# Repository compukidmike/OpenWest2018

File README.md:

# OpenWest2018 Electronic Badge

## This year's badge is dedicated to our dear friend d3c4f. May his memory live on through many more awesome badges. 

The 2018 badge features WiFi connectivity, and all the badges are controlled by an MQTT server. The main controller is a WeMos D1 Mini, which uses the ESP8266 WiFi module.

**A note on battery life:** WiFi uses a lot of power. So do LEDs. The badges probably won't last more than a day on batteries. Take them out when you're not at the conference to avoid unnecessary battery drain. **Also, don't connect a USB cable while the batteries are in the badge. Bad things could happen.**

One of the fun things about this badge is that they're all controlled by this central server. There's no authentication on MQTT publications, so anyone can change what all the badges are doing. There are many programs to interact with MQTT servers. MQTTLens is a free chrome app that's very easy to use. If you want to learn more about MQTT go here https://www.hivemq.com/blog/mqtt-essentials-part-1-introducing-mqtt

We're using mosquitto (https://mosquitto.org/) for our local MQTT server. This server is only available at the conference. After the con is over, you'll have to connect the badge to your own server or an online service like adafruit.io. There are instructions below on how to do that.

The local MQTT server IP is 10.155.0.214, port 1883

The Feeds are setup as follows:
- Feed names: color1, color2, effect, effectspeed
- All feeds are prefixed by `feeds/`
- Colors are in Hex format (FFFFFF)
- Effectspeed is 0-255
- Effect is 0-6 (Off, On, Blink, Pulse, Alternate1, Alternate2, Rainbow)
- Must set retain flag on messages

The retain flag is important. It tells the server to keep the last message, and give it to any new client that subscribes to a feed. That means your badge won't have to wait until a new message is sent out to start displaying the proper colors, etc.

----------

## To get the Arduino IDE set up, you'll need to do the following:
(The Arduino IDE can be downloaded from https://www.arduino.cc/)
- Add the ESP8266 to the boards menu
  - From the Arduino IDE, click on File -> Preferences
  - Add this URL to the "Additional Boards Manager URLs" http://arduino.esp8266.com/stable/package_esp8266com_index.json
  - Click OK
  - Click on Tools > Board > Board Manager
  - Type ESP8266 in the search box
  - Find ESP8266 in the list and click Install
  
- Add the required libraries
  - Click Sketch > Include Library > Manage Libraries...
  - Search for and install the following libraries:
    - Adafruit IO Arduino
    - Adafruit MQTT Library
    - ArduinoHTTPClient
    - FastLED
    - WiFi
- Mac users need to download the WeMos driver at: https://wiki.wemos.cc/downloads (restart required after install).

## To connect the badge to your own WiFi network:
- Edit the following lines in the code:
  ```
  #define WLAN_SSID       "OPENWEST-GUEST"
  #define WLAN_PASS       "Openwest2018!"
  ```

## To connect the badge to a different MQTT server:
- Edit the following lines in the code:
  ```
  #define AIO_SERVER      "10.155.0.214"         // IP or URL for MQTT server
  #define AIO_SERVERPORT  1883                   // use 8883 for SSL
  #define AIO_USERNAME    "test"                 // Adafruit.io username
  #define AIO_KEY         "1234567890"           // Adafruit.io key
  ```
- To connect to adafruit.io, you'll need to create an account and then put your username and AIO key here. There are also more steps below for adafruit.io

## Adafruit.io Workaround
If you attended my talk about the badge, I talked about how adafruit.io is an MQTT server that doesn't fit the spec. One of the things I said was that they retain messages by default. Well, they changed that, but still don't support the retain flag, so there's a workaround. Please keep in mind that they made this change on April 22, 2018. I've been working with the badge code since long before that. They've updated their libraries to handle this, but I haven't had a chance to mess with it. If you get it working with the new Adafruit IO library, please submit a pull request.
Here's the blog post that talks about the change: https://io.adafruit.com/blog/notebook/2018/04/22/new-io-plus-and-mqtt-features/

### So, with that said, here's the workaround:
- All feed names are prefixed by your username, so they look like this: `<username>/feeds/<feed_name>`
- You'll need to set up a publish feed for each of your feed subscriptions with `/get` at the end (I know, it's ridiculous).
  - Example: ```Adafruit_MQTT_Publish color1get = Adafruit_MQTT_Publish(&mqtt, AIO_USERNAME "/feeds/color1/get");```
  - Note that the name must be different from the feed subscription (color1get vs color1)
- Then, near the bottom of the code after this line: ```Serial.println("MQTT Connected!");```
  - Add a publish for each feed:
    ```
    color1get.publish('\0');
    color2get.publish('\0');
    effectget.publish('\0');
    effectspeedget.publish('\0');
    delay(1000); //delay for receiving the packets
    ```
  - The delay is necessary to give time to get the response from the server and not drop packets
  
I know this is an ugly workaround. I'm sorry. On the bright side, it does show how to setup and publish data back to the server.

----------

If I missed anything, or you have something to add to this readme, please submit a pull request.

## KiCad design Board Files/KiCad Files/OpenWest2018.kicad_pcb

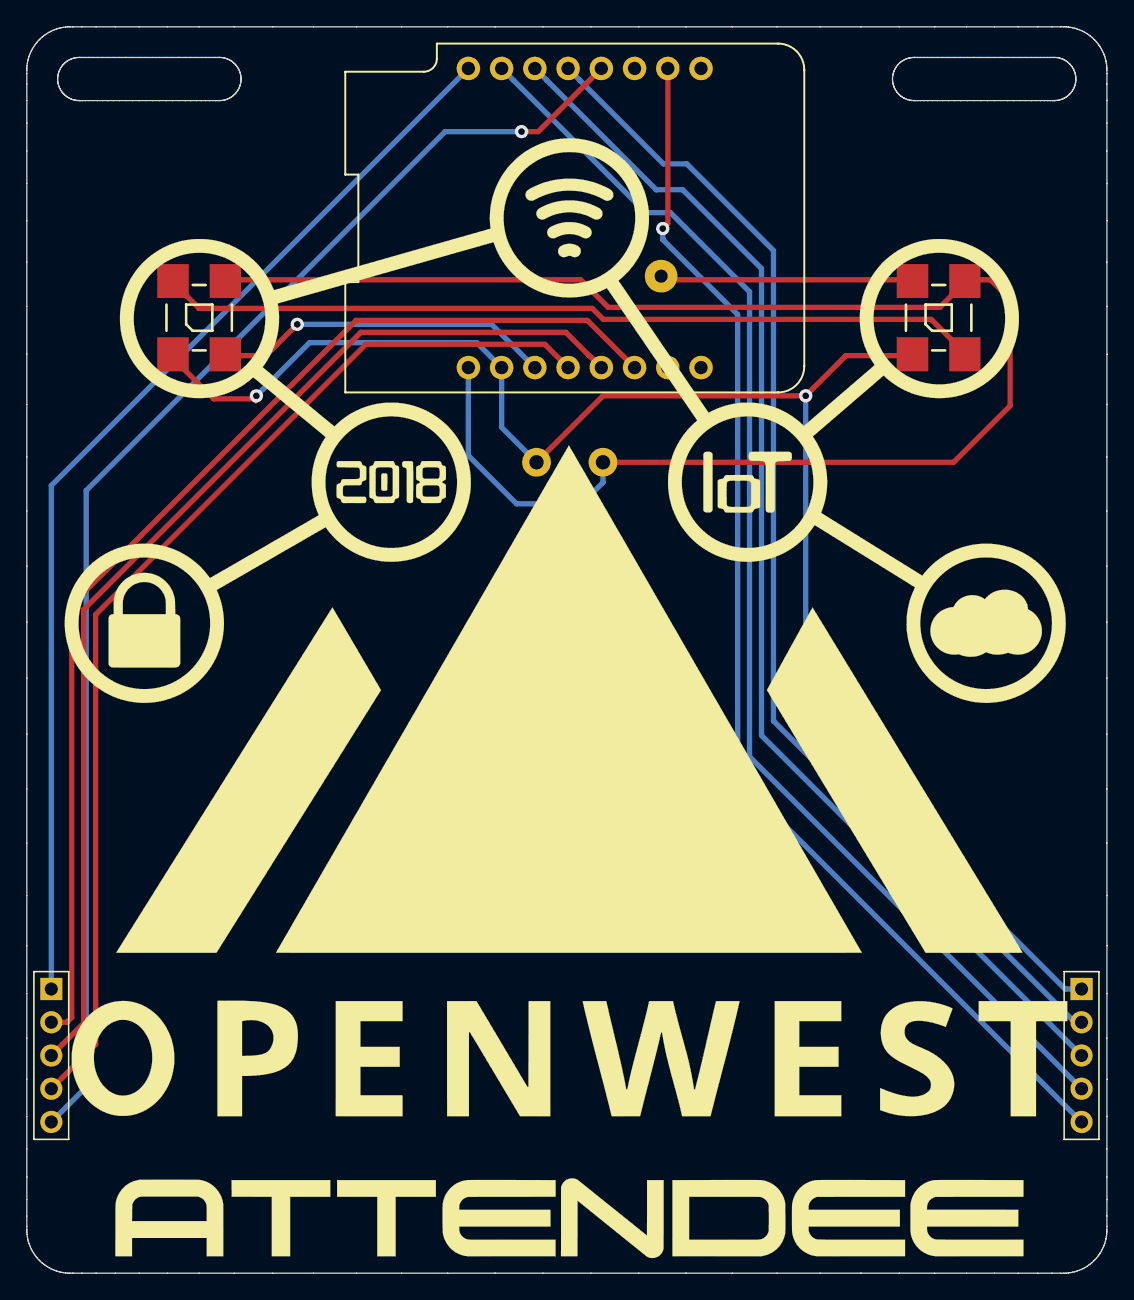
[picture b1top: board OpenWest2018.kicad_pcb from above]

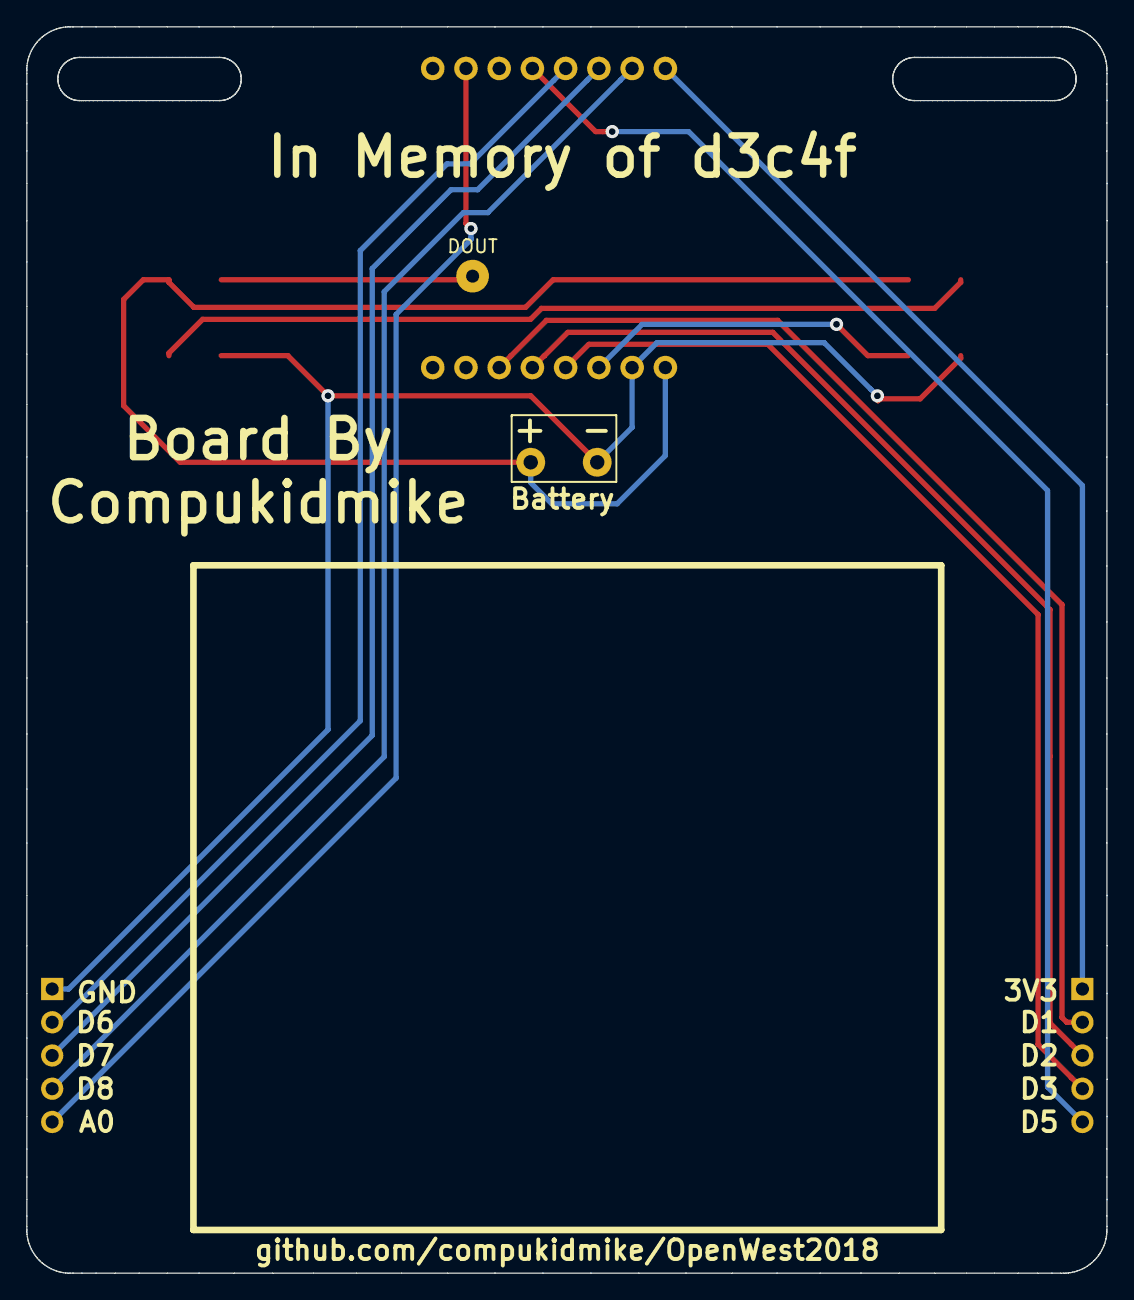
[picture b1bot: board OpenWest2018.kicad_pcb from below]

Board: 2 copper layers, 82.5 x 95.3 mm, 7 parts (2 on the bottom side), 15 nets.

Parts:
BT1: Battery; Battery-WireConn
DOUT: TEST; SolderWirePad_single_1mmDrill
J1, J2: Conn_01x05; Socket_Strip_Straight_1x05_Pitch2.54mm
LED1, LED2: WS2812B
U1: WeMos_mini; wemos-d1-mini-with-pin-header-and-connector

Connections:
+3V3: J1.1, U1.16
+BATT: BT1.1, LED1.1, LED2.1, U1.1
A0: J2.5, U1.10
D1: J1.2, U1.6
D2: J1.3, U1.5
D3: J1.4, U1.4
D5: J1.5, U1.12
D6: J2.2, U1.13
D7: J2.3, U1.14
D8: J2.4, U1.15
GND: BT1.2, J2.1, LED1.3, LED2.3, U1.2
unnamed: DOUT.1, LED2.2
unnamed: LED1.2, LED2.4
unnamed: LED1.4, U1.3
unnamed: U1.9, U1.11

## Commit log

2018-06-07 add arduino file folder
2018-06-08 Added Mac WeMos driver download link.
2018-06-08 add for loop for multiple leds
2018-07-09 Add board files
2018-07-09 added schematic pdf
